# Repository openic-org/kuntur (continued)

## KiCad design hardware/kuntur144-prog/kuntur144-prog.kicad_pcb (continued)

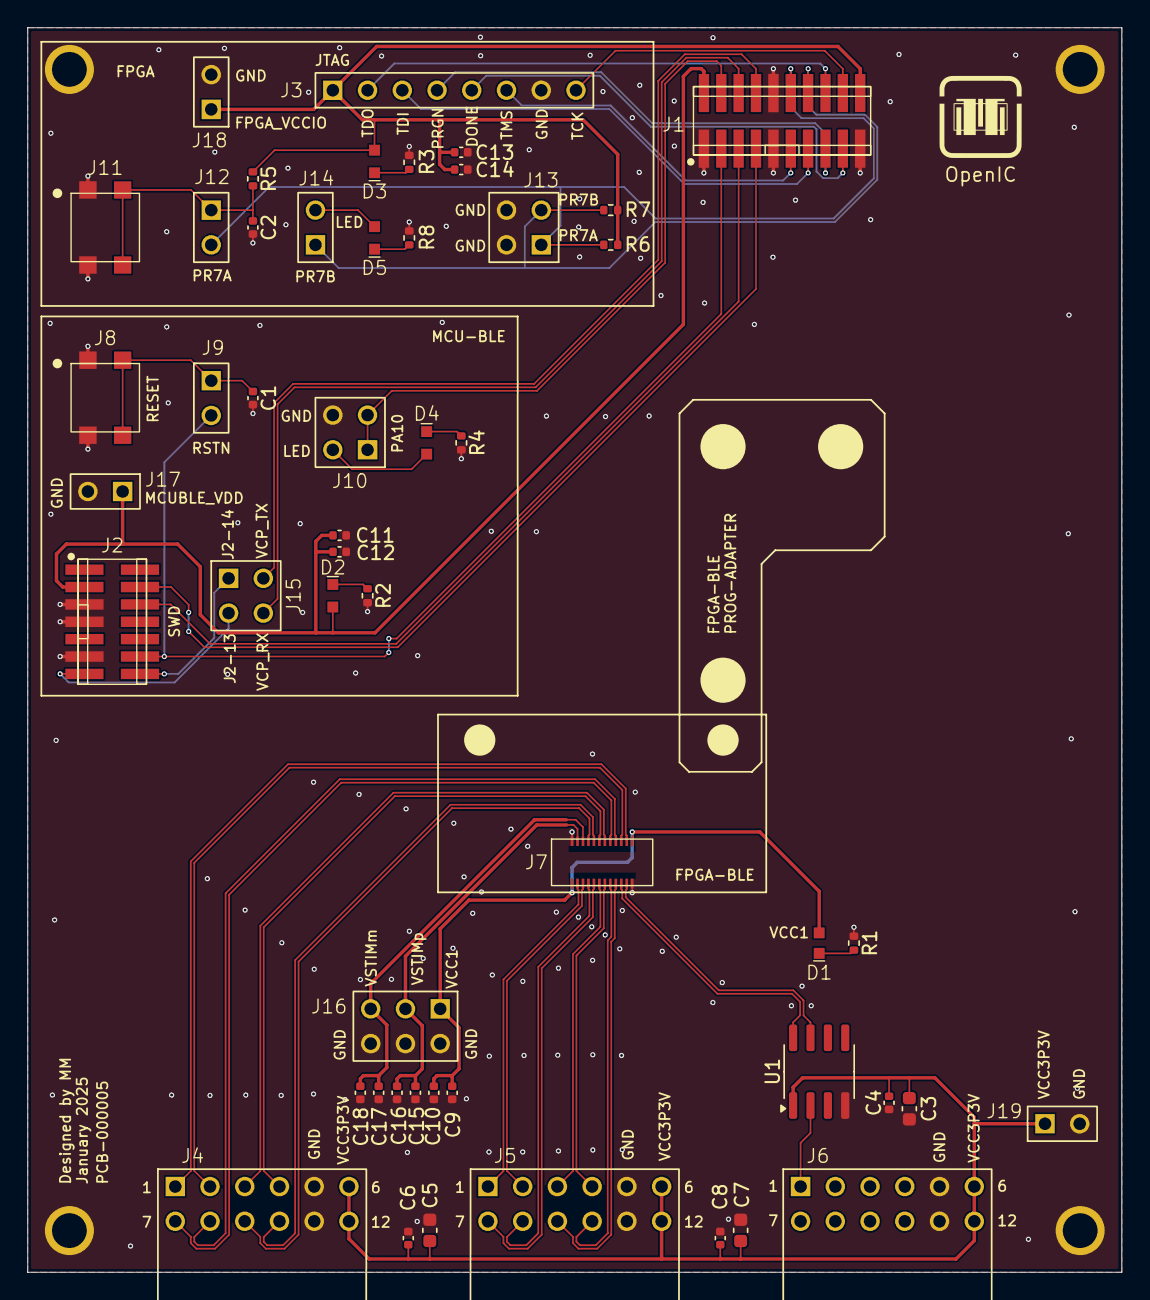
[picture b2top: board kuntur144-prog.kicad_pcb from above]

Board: 2 copper layers, 80.0 x 91.0 mm, 55 parts (0 on the bottom side), 51 nets.

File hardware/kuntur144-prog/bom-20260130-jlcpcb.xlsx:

Designator | Comment | Footprint
C1,C2,C4,C6,C8,C10,C12,C14,C16,C18 | 100n | GRM155R61C104KA88D
C3,C5,C7 | 10u | GRM185R60J106ME15J
C9,C11,C13,C15,C17 | 1u | GRM155R61C105KA12J
D1 | SMT Diode | LGQ396
D2,D3,D4,D5 | SMT Diode | CSL1901UW1
J1 | Connector | FTSH-110-01-L-DV-K
J2 | Connector | FTSH-107-01-L-DV-K
J3 | Headers | PH1-08-UA
J4,J5,J6 | Headers | PH2RA-12-UA
J7 | Connector | DF40C(2.0)-24DS-0.4V(51)
J8,J11 | Push-button | 7914G-1-000
J9,J12,J14,J17,J18,J19 | Headers | PH1-02-UA
J10,J13,J15 | Headers | M20-9760246
J16 | Headers | M20-9980346
R1,R2,R3,R4,R8 | 10 | RC0402FR-7W10RL
R5 | 10k | RC0402FR-7W10KL
R6,R7 | Do not populate | RC0402FR-7W4K7L
S1,S2,S3,S4 |  | None
U1 | LVDS to CMOS | ADN4661BRZ-REEL7

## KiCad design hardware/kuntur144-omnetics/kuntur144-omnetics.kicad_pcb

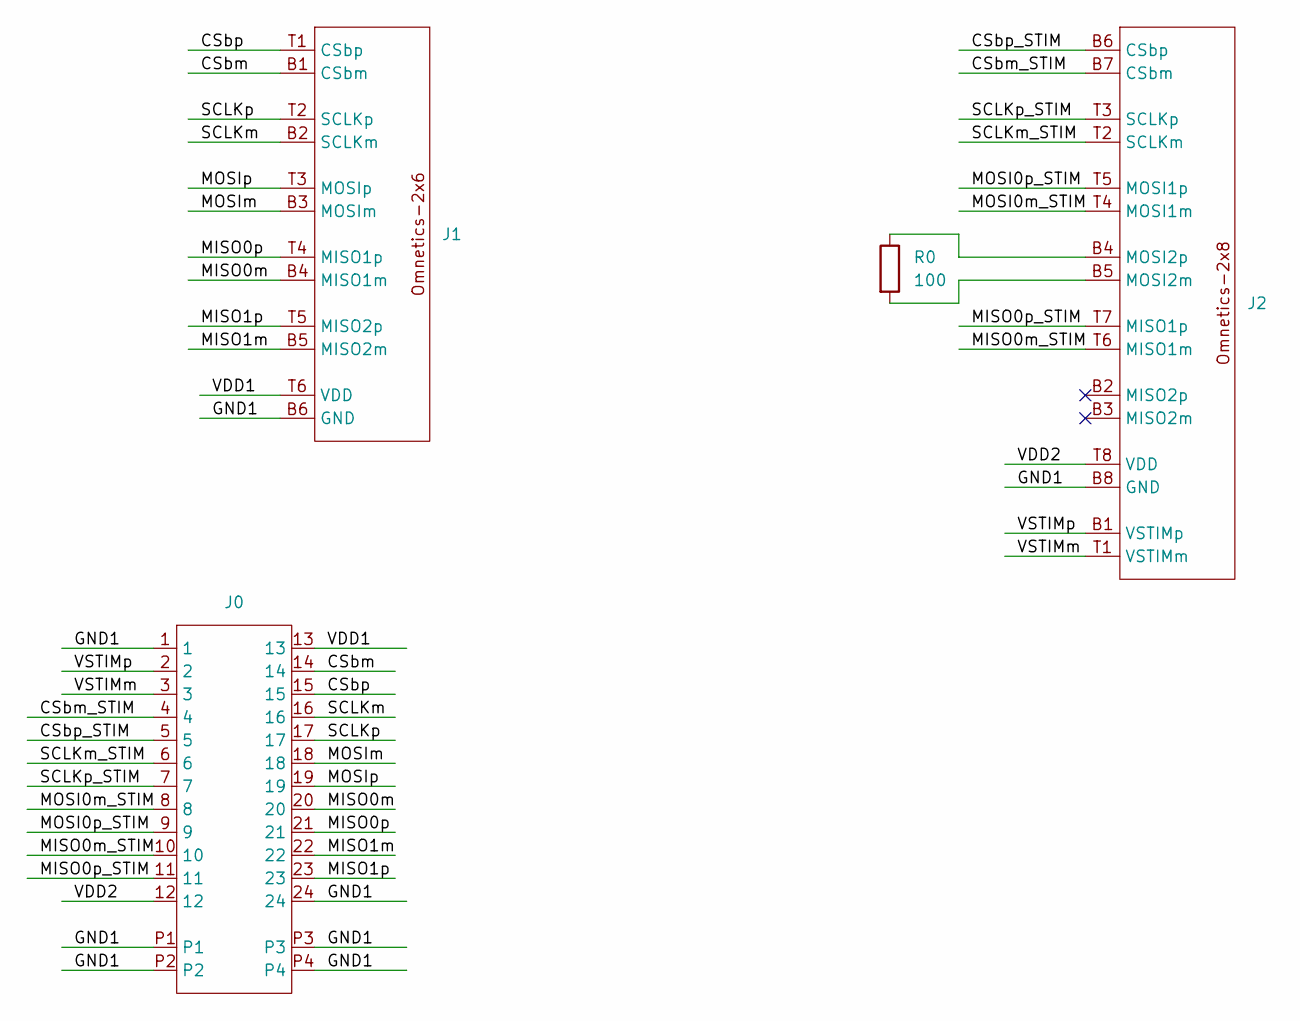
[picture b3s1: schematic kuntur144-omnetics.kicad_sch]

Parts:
J0: DF40C(2.0)-24DP-0.4V
J1: OMNETICS_PZN-12-AA; MPN A79623-001
J2: OMNETICS_PZN-16-AA; MPN A79633-001
R0: 100; R_0402_1005Metric

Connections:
/CSbm: J0.14, J1.B1 (CSbm)
/CSbm_STIM: J0.4, J2.B7 (CSbm)
/CSbp: J0.15, J1.T1 (CSbp)
/CSbp_STIM: J0.5, J2.B6 (CSbp)
/GND1: J0.1, J0.24, J0.P1, J0.P2, J0.P3, J0.P4, J1.B6 (GND), J2.B8 (GND)
/MISO0m: J0.20, J1.B4 (MISO1m)
/MISO0m_STIM: J0.10, J2.T6 (MISO1m)
/MISO0p: J0.21, J1.T4 (MISO1p)
/MISO0p_STIM: J0.11, J2.T7 (MISO1p)
/MISO1m: J0.22, J1.B5 (MISO2m)
/MISO1p: J0.23, J1.T5 (MISO2p)
/MOSI0m_STIM: J0.8, J2.T4 (MOSI1m)
/MOSI0p_STIM: J0.9, J2.T5 (MOSI1p)
/MOSIm: J0.18, J1.B3 (MOSIm)
/MOSIp: J0.19, J1.T3 (MOSIp)
/SCLKm: J0.16, J1.B2 (SCLKm)
/SCLKm_STIM: J0.6, J2.T2 (SCLKm)
/SCLKp: J0.17, J1.T2 (SCLKp)
/SCLKp_STIM: J0.7, J2.T3 (SCLKp)
/VDD1: J0.13, J1.T6 (VDD)
/VDD2: J0.12, J2.T8 (VDD)
/VSTIMm: J0.3, J2.T1 (VSTIMm)
/VSTIMp: J0.2, J2.B1 (VSTIMp)
unnamed: J2.B5 (MOSI2m), R0.2
unnamed: J2.B4 (MOSI2p), R0.1

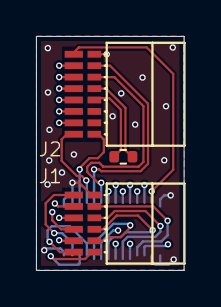
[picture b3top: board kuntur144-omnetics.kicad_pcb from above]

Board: 4 copper layers, 8.2 x 13.0 mm, 4 parts (1 on the bottom side), 25 nets.

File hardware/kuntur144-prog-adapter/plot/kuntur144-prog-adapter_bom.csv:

"Reference","Value","Qty","DNP","Manufacturer","MPN"
"J1","~","1","","Molex","5052742012"
"J2","~","1","","Samtec","FTSH-110-01-L-DV-K"

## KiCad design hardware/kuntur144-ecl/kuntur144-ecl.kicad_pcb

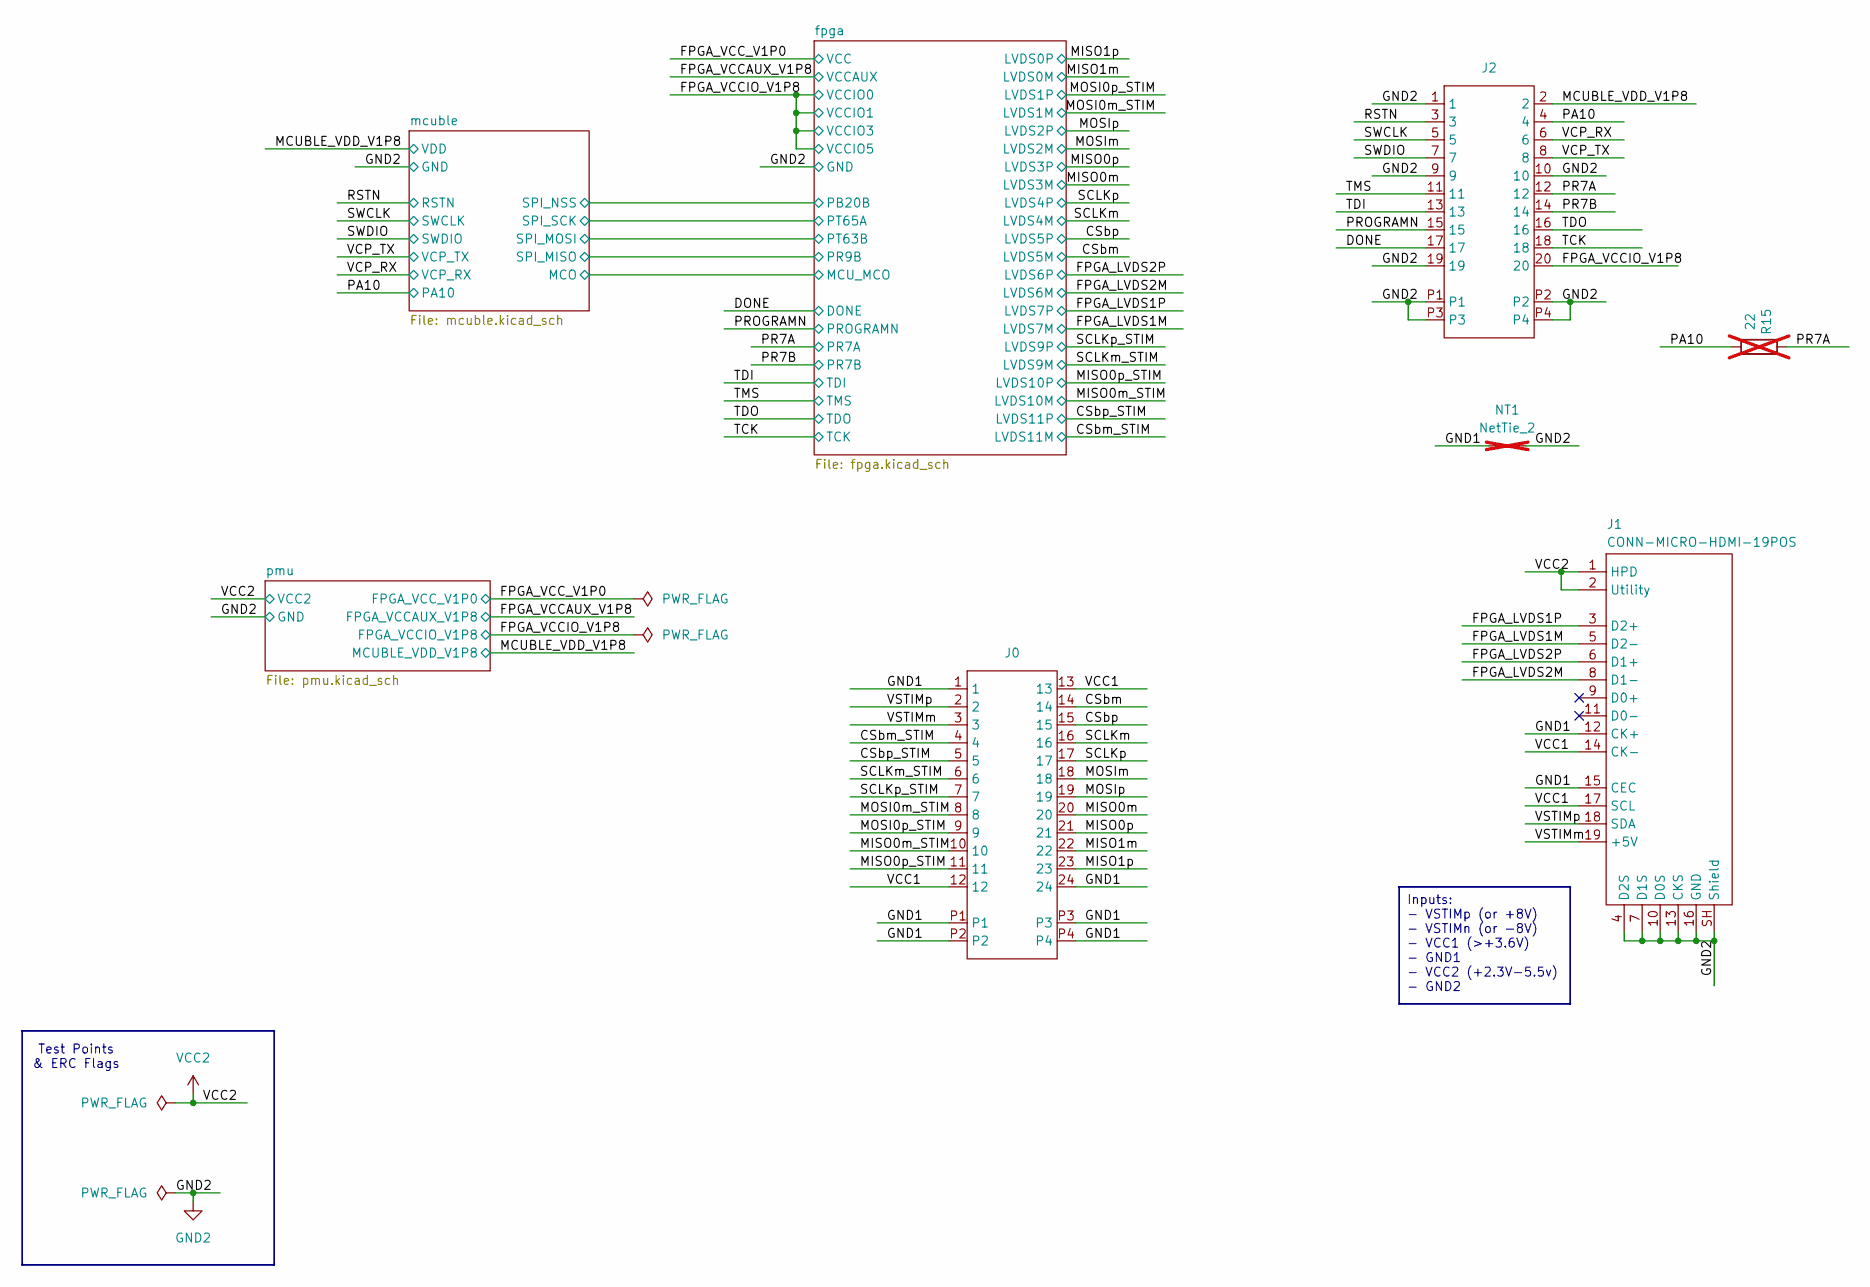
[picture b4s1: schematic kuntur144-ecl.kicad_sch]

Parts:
J0: DF40C(2.0)-24DP-0.4V; MPN DF40C-24DP-0.4V(51)
J1: CONN-MICRO-HDMI-19POS; HDMI_Micro-D_Molex_46765-0x01; MPN 0467650001
J2: CONN-MOLEX-MEZZ-20POS-P0.35mm; MPN 5052702012
NT1: NetTie_2; NetTie-2_SMD; not fitted
R15: 22; R_0402_1005Metric; MPN RC0402FR-0722RL; not fitted

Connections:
/CSbm: J0.14; also elsewhere on the board
/CSbm_STIM: J0.4; also elsewhere on the board
/CSbp: J0.15; also elsewhere on the board
/CSbp_STIM: J0.5; also elsewhere on the board
/DONE: J2.17; also elsewhere on the board
/FPGA_LVDS1M: J1.5 (D2-); also elsewhere on the board
/FPGA_LVDS1P: J1.3 (D2+); also elsewhere on the board
/FPGA_LVDS2M: J1.8 (D1-); also elsewhere on the board
/FPGA_LVDS2P: J1.6 (D1+); also elsewhere on the board
/FPGA_VCCIO_V1P8: J2.20; also elsewhere on the board
/GND1: J0.1, J0.24, J0.P1, J0.P2, J0.P3, J0.P4, J1.12 (CK+), J1.15 (CEC), NT1.1
/MCUBLE_VDD_V1P8: J2.2; also elsewhere on the board
/MISO0m: J0.20; also elsewhere on the board
/MISO0m_STIM: J0.10; also elsewhere on the board
/MISO0p: J0.21; also elsewhere on the board
/MISO0p_STIM: J0.11; also elsewhere on the board
/MISO1m: J0.22; also elsewhere on the board
/MISO1p: J0.23; also elsewhere on the board
/MOSI0m_STIM: J0.8; also elsewhere on the board
/MOSI0p_STIM: J0.9; also elsewhere on the board
/MOSIm: J0.18; also elsewhere on the board
/MOSIp: J0.19; also elsewhere on the board
/PA10: J2.4, R15.1; also elsewhere on the board
/PR7A: J2.12, R15.2; also elsewhere on the board
/PR7B: J2.14; also elsewhere on the board
/PROGRAMN: J2.15; also elsewhere on the board
/RSTN: J2.3; also elsewhere on the board
/SCLKm: J0.16; also elsewhere on the board
/SCLKm_STIM: J0.6; also elsewhere on the board
/SCLKp: J0.17; also elsewhere on the board
/SCLKp_STIM: J0.7; also elsewhere on the board
/SWCLK: J2.5; also elsewhere on the board
/SWDIO: J2.7; also elsewhere on the board
/TCK: J2.18; also elsewhere on the board
/TDI: J2.13; also elsewhere on the board
/TDO: J2.16; also elsewhere on the board
/TMS: J2.11; also elsewhere on the board
/VCC1: J0.12, J0.13, J1.14 (CK-), J1.17 (SCL)
/VCP_RX: J2.6; also elsewhere on the board
/VCP_TX: J2.8; also elsewhere on the board
/VSTIMm: J0.3, J1.19 (+5V)
/VSTIMp: J0.2, J1.18 (SDA)
GND2: J1.4 (D2S), J1.7 (D1S), J1.10 (D0S), J1.13 (CKS), J1.16 (GND), J1.SH (Shield), J2.1, J2.9, J2.10, J2.19, J2.P1, J2.P2, J2.P3, J2.P4, NT1.2; also elsewhere on the board
VCC2: J1.1 (HPD), J1.2 (Utility); also elsewhere on the board

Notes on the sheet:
Inputs: - VSTIMp (or +8V) - VSTIMn (or -8V) - VCC1 (>+3.6V) - GND1 - VCC2 (+2.3V-5.5v) - GND2
Test Points & ERC Flags

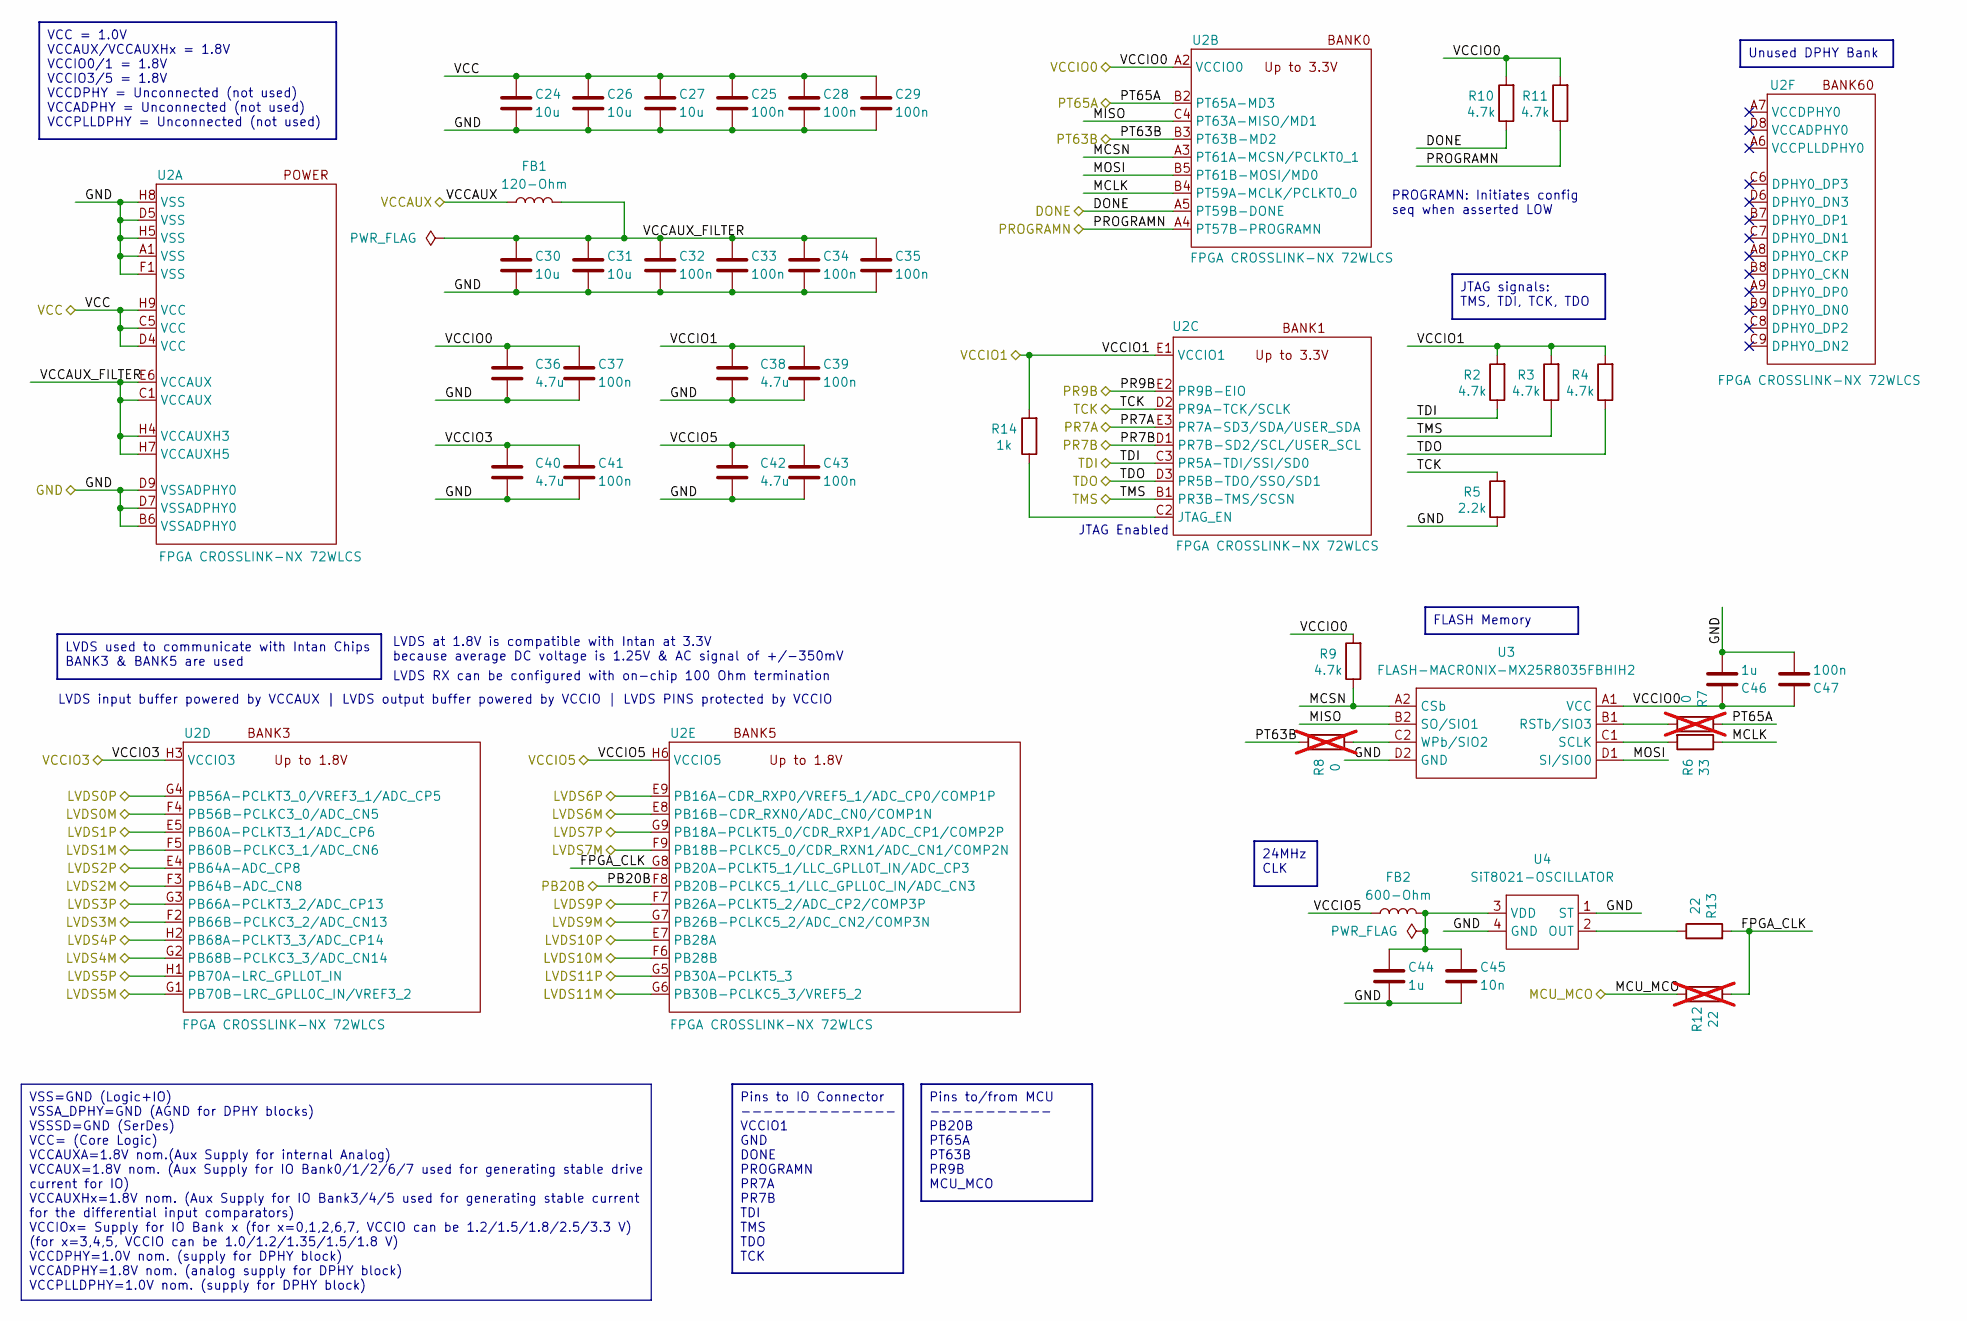
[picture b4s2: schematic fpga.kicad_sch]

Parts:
C24, C26, C27, C30, C31: 10u; SMD_C_0603_10UF_6.3V_GRM185R60J106ME15; MPN GRM185R60J106ME15J
C25, C28, C29, C32, C33, C34, C35, C37, C39, C41, C43, C47: 100n; C_0201_0603Metric; MPN C0603X5R1C104K030BC
C36, C38, C40, C42: 4.7u; C_0402_1005Metric; MPN KGM05CR51C475MH
C44, C46: 1u; C_0201_0603Metric; MPN GRM033R61C105ME15D
C45: 10n; C_0201_0603Metric; MPN GRM033R61C103KA12D
FB1: 120-Ohm; L_0402_1005Metric; MPN MPZ1005S121CT000
FB2: 600-Ohm; L_0402_1005Metric; MPN BLM15AX601SN1D
R2, R3, R4, R9, R10, R11: 4.7k; R_0201_0603Metric; MPN RC0201FR-074K7L
R5: 2.2k; R_0201_0603Metric; MPN RC0201FR-072K2L
R6: 33; R_0201_0603Metric; MPN RC0201FR-0733RL
R7, R8: 0; R_0201_0603Metric; MPN RC0201FR-070RL; not fitted
R12: 22; R_0402_1005Metric; MPN RC0402FR-0722RL; not fitted
R13: 22; R_0402_1005Metric; MPN RC0402FR-0722RL
R14: 1k; R_0201_0603Metric; MPN RC0201FR-071KL
U2: BGA-72_9x8_4.1x3.8mm; MPN LIFCL-17-7UWG72C
U3: FLASH-MACRONIX-MX25R8035FBHIH2; MX25R8035FBHIH2-WLCSP-8; MPN MX25R8035FBHIH2
U4: SiT8021-OSCILLATOR; SiTime-4LD-1.5x0.8x0.55mm; MPN SIT8021AC-J4-18S-24.000000

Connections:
/CSbm: U2.G1 (PB70B-LRC_GPLL0C_IN/VREF3_2); also elsewhere on the board
/CSbm_STIM: U2.G6 (PB30B-PCLKC5_3/VREF5_2); also elsewhere on the board
/CSbp: U2.H1 (PB70A-LRC_GPLL0T_IN); also elsewhere on the board
/CSbp_STIM: U2.G5 (PB30A-PCLKT5_3); also elsewhere on the board
/DONE: R10.1, U2.A5 (PT59B-DONE); also elsewhere on the board
/FPGA_LVDS1M: U2.F9 (PB18B-PCLKC5_0/CDR_RXN1/ADC_CN1/COMP2N); also elsewhere on the board
/FPGA_LVDS1P: U2.G9 (PB18A-PCLKT5_0/CDR_RXP1/ADC_CP1/COMP2P); also elsewhere on the board
/FPGA_LVDS2M: U2.E8 (PB16B-CDR_RXN0/ADC_CN0/COMP1N); also elsewhere on the board
/FPGA_LVDS2P: U2.E9 (PB16A-CDR_RXP0/VREF5_1/ADC_CP0/COMP1P); also elsewhere on the board
/FPGA_VCCAUX_V1P8: FB1.2; also elsewhere on the board
/FPGA_VCCIO_V1P8: C36.1, C37.1, C38.1, C39.1, C40.1, C41.1, C42.1, C43.1, C46.1, C47.1, FB2.2, R2.2, R3.2, R4.2, R9.2, R10.2, R11.2, R14.2, U2.A2 (VCCIO0), U2.E1 (VCCIO1), U2.H3 (VCCIO3), U2.H6 (VCCIO5), U3.A1 (VCC); also elsewhere on the board
/FPGA_VCC_V1P0: C24.1, C25.1, C26.1, C27.1, C28.1, C29.1, U2.C5 (VCC), U2.D4 (VCC), U2.H9 (VCC); also elsewhere on the board
/MISO0m: U2.F2 (PB66B-PCLKC3_2/ADC_CN13); also elsewhere on the board
/MISO0m_STIM: U2.F6 (PB28B); also elsewhere on the board
/MISO0p: U2.G3 (PB66A-PCLKT3_2/ADC_CP13); also elsewhere on the board
/MISO0p_STIM: U2.E7 (PB28A); also elsewhere on the board
/MISO1m: U2.F4 (PB56B-PCLKC3_0/ADC_CN5); also elsewhere on the board
/MISO1p: U2.G4 (PB56A-PCLKT3_0/VREF3_1/ADC_CP5); also elsewhere on the board
/MOSI0m_STIM: U2.F5 (PB60B-PCLKC3_1/ADC_CN6); also elsewhere on the board
/MOSI0p_STIM: U2.E5 (PB60A-PCLKT3_1/ADC_CP6); also elsewhere on the board
/MOSIm: U2.F3 (PB64B-ADC_CN8); also elsewhere on the board
/MOSIp: U2.E4 (PB64A-ADC_CP8); also elsewhere on the board
/PR7A: U2.E3 (PR7A-SD3/SDA/USER_SDA); also elsewhere on the board
/PR7B: U2.D1 (PR7B-SD2/SCL/USER_SCL); also elsewhere on the board
/PROGRAMN: R11.1, U2.A4 (PT57B-PROGRAMN); also elsewhere on the board
/SCLKm: U2.G2 (PB68B-PCLKC3_3/ADC_CN14); also elsewhere on the board
/SCLKm_STIM: U2.G7 (PB26B-PCLKC5_2/ADC_CN2/COMP3N); also elsewhere on the board
/SCLKp: U2.H2 (PB68A-PCLKT3_3/ADC_CP14); also elsewhere on the board
/SCLKp_STIM: U2.F7 (PB26A-PCLKT5_2/ADC_CP2/COMP3P); also elsewhere on the board
/TCK: R5.2, U2.D2 (PR9A-TCK/SCLK); also elsewhere on the board
/TDI: R2.1, U2.C3 (PR5A-TDI/SSI/SD0); also elsewhere on the board
/TDO: R4.1, U2.D3 (PR5B-TDO/SSO/SD1); also elsewhere on the board
/TMS: R3.1, U2.B1 (PR3B-TMS/SCSN); also elsewhere on the board
/fpga/FPGA_CLK: R12.1, R13.2, U2.G8 (PB20A-PCLKT5_1/LLC_GPLL0T_IN/ADC_CP3)
/fpga/MCLK: R6.1, U2.B4 (PT59A-MCLK/PCLKT0_0)
/fpga/MCSN: R9.1, U2.A3 (PT61A-MCSN/PCLKT0_1), U3.A2 (CSb)
/fpga/MCU_MCO: R12.2; also elsewhere on the board
/fpga/MISO: U2.C4 (PT63A-MISO/MD1), U3.B2 (SO/SIO1)
/fpga/MOSI: U2.B5 (PT61B-MOSI/MD0), U3.D1 (SI/SIO0)
/fpga/PB20B: U2.F8 (PB20B-PCLKC5_1/LLC_GPLL0C_IN/ADC_CN3); also elsewhere on the board
/fpga/PR9B: U2.E2 (PR9B-EIO); also elsewhere on the board
/fpga/PT63B: R8.2, U2.B3 (PT63B-MD2); also elsewhere on the board
/fpga/PT65A: R7.2, U2.B2 (PT65A-MD3); also elsewhere on the board
/fpga/VCCAUX_FILTER: C30.1, C31.1, C32.1, C33.1, C34.1, C35.1, FB1.1, U2.C1 (VCCAUX), U2.E6 (VCCAUX), U2.H4 (VCCAUXH3), U2.H7 (VCCAUXH5)
GND2: C24.2, C25.2, C26.2, C27.2, C28.2, C29.2, C30.2, C31.2, C32.2, C33.2, C34.2, C35.2, C36.2, C37.2, C38.2, C39.2, C40.2, C41.2, C42.2, C43.2, C44.2, C45.2, C46.2, C47.2, R5.1, U2.A1 (VSS), U2.B6 (VSSADPHY0), U2.D5 (VSS), U2.D7 (VSSADPHY0), U2.D9 (VSSADPHY0), U2.F1 (VSS), U2.H5 (VSS), U2.H8 (VSS), U3.D2 (GND), U4.1 (ST), U4.4 (GND); also elsewhere on the board
unnamed: R14.1, U2.C2 (JTAG_EN)
unnamed: R7.1, U3.B1 (RSTb/SIO3)
unnamed: R6.2, U3.C1 (SCLK)
unnamed: R8.1, U3.C2 (WPb/SIO2)
unnamed: R13.1, U4.2 (OUT)
unnamed: C44.1, C45.1, FB2.1, U4.3 (VDD)

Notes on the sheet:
VSS=GND (Logic+IO) VSSA_DPHY=GND (AGND for DPHY blocks) VSSSD=GND (SerDes) VCC= (Core Logic) VCCAUXA=1.8V nom.(Aux Supply for internal Analog) VCCAUX=1.8V nom. (Aux Supply for IO Bank0/1/2/6/7 used for generating stable drive current for IO) VCCAUXHx=1.8V nom. (Aux Supply for IO Bank3/4/5 used for 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
FLASH Memory
24MHz CLK
VCC = 1.0V VCCAUX/VCCAUXHx = 1.8V VCCIO0/1 = 1.8V VCCIO3/5 = 1.8V VCCDPHY = Unconnected (not used) VCCADPHY = Unconnected (not used) VCCPLLDPHY = Unconnected (not used)
Pins to IO Connector -------------- VCCIO1 GND DONE PROGRAMN PR7A PR7B TDI TMS TDO TCK
JTAG signals: TMS, TDI, TCK, TDO
Pins to/from MCU ----------- PB20B PT65A PT63B PR9B MCU_MCO
LVDS used to communicate with Intan Chips BANK3 & BANK5 are used
Unused DPHY Bank
JTAG Enabled
PROGRAMN: Initiates config seq when asserted LOW
LVDS RX can be configured with on-chip 100 Ohm termination
LVDS input buffer powered by VCCAUX | LVDS output buffer powered by VCCIO | LVDS PINS protected by VCCIO
LVDS at 1.8V is compatible with Intan at 3.3V because average DC voltage is 1.25V & AC signal of +/-350mV

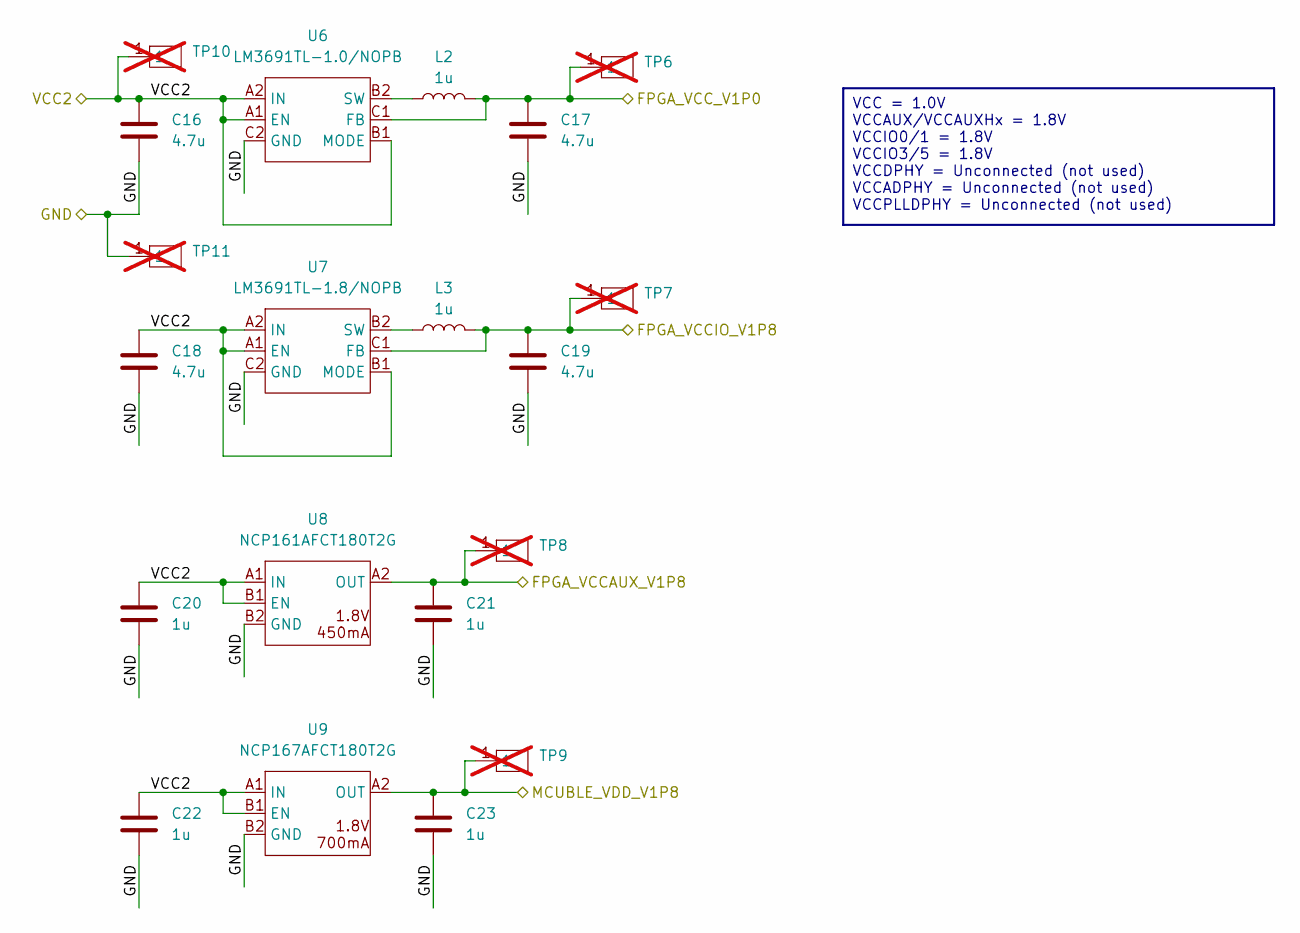
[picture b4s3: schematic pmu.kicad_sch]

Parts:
C16, C17, C18, C19: 4.7u; C_0402_1005Metric; MPN KGM05CR51C475MH
C20, C21, C22, C23: 1u; C_0201_0603Metric; MPN GRM033R61C105ME15D
L2, L3: 1u; SMD_L_0805_1UH_MLZ2012; MPN MLZ2012A1R0WT000
TP6, TP7, TP8, TP9, TP10, TP11: TESTPOINT_PAD_SQ_0.5; not fitted
U6: LM3691TL-1.0/NOPB; DSBGA-6-P0.5; MPN LM3691TL-1.0/NOPB
U7: LM3691TL-1.8/NOPB; DSBGA-6-P0.5; MPN LM3691TL-1.8/NOPB
U8: NCP161AFCT180T2G; WLCSP-4-P0.35; MPN NCP161AFCT180T2G
U9: NCP167AFCT180T2G; WLCSP-4-P0.35; MPN NCP167AFCT180T2G

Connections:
/FPGA_VCCAUX_V1P8: C21.1, TP8.1, U8.A2 (OUT); also elsewhere on the board
/FPGA_VCCIO_V1P8: C19.1, L3.2, TP7.1, U7.C1 (FB); also elsewhere on the board
/FPGA_VCC_V1P0: C17.1, L2.2, TP6.1, U6.C1 (FB); also elsewhere on the board
/MCUBLE_VDD_V1P8: C23.1, TP9.1, U9.A2 (OUT); also elsewhere on the board
GND2: C16.2, C17.2, C18.2, C19.2, C20.2, C21.2, C22.2, C23.2, TP11.1, U6.C2 (GND), U7.C2 (GND), U8.B2 (GND), U9.B2 (GND); also elsewhere on the board
unnamed: L2.1, U6.B2 (SW)
unnamed: L3.1, U7.B2 (SW)
VCC2: C16.1, C18.1, C20.1, C22.1, TP10.1, U6.A1 (EN), U6.A2 (IN), U6.B1 (MODE), U7.A1 (EN), U7.A2 (IN), U7.B1 (MODE), U8.A1 (IN), U8.B1 (EN), U9.A1 (IN), U9.B1 (EN); also elsewhere on the board

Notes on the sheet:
VCC = 1.0V VCCAUX/VCCAUXHx = 1.8V VCCIO0/1 = 1.8V VCCIO3/5 = 1.8V VCCDPHY = Unconnected (not used) VCCADPHY = Unconnected (not used) VCCPLLDPHY = Unconnected (not used)

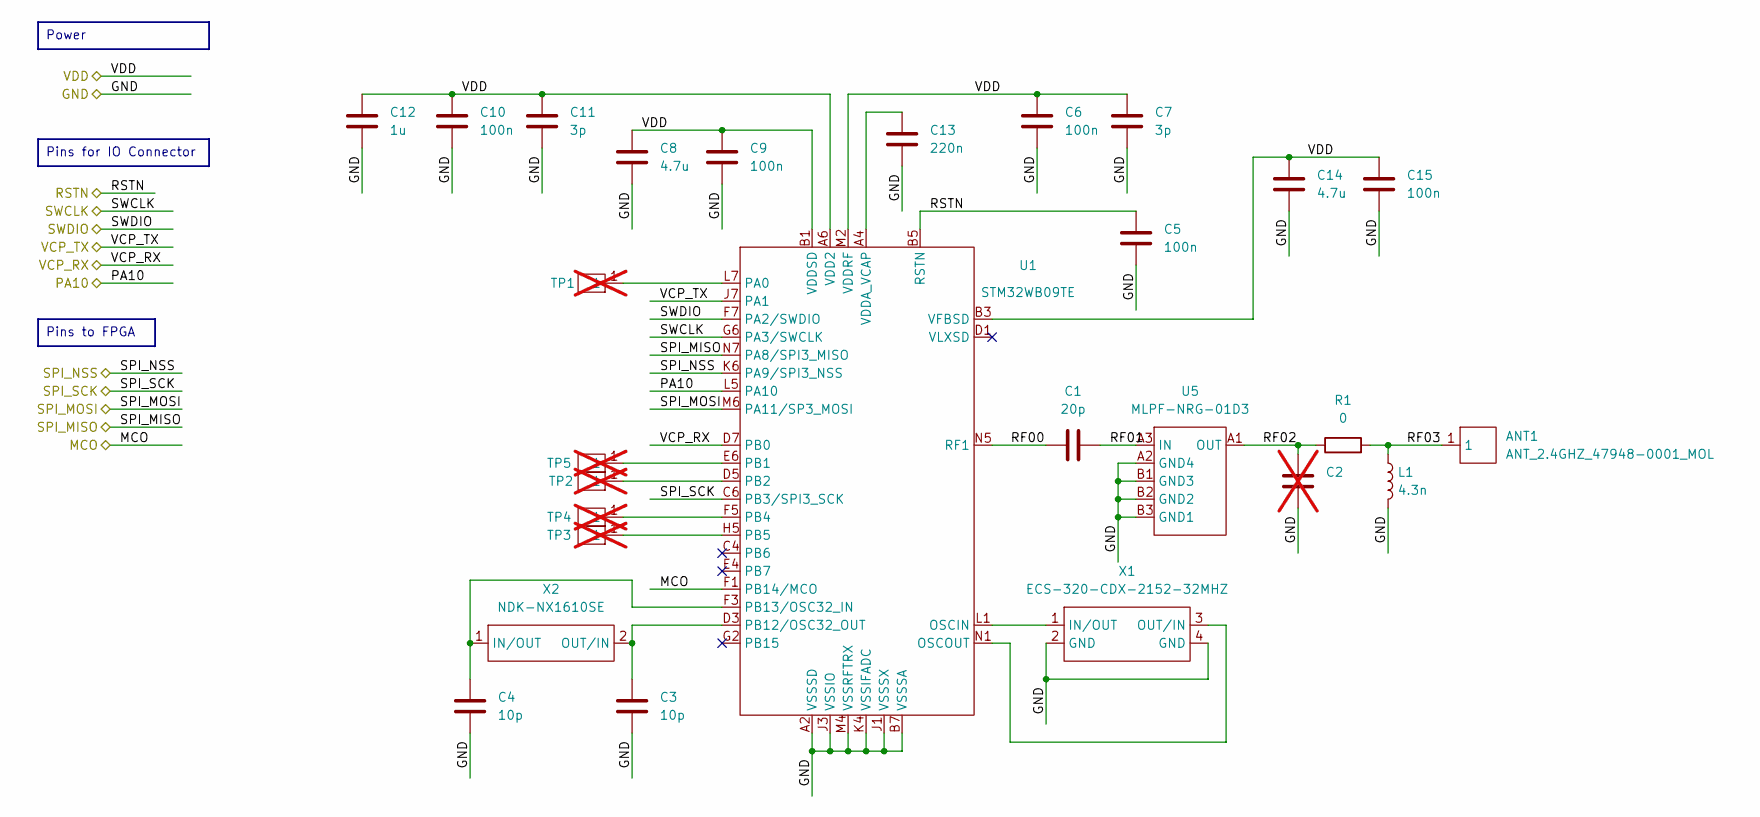
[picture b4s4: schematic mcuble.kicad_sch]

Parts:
ANT1: ANT_2.4GHZ_47948-0001_MOL; ANT_47948-0001_MOL; MPN 0479480001
C1: 20p; SMD-0201; MPN GJM0335C1E200GB01
C2: SMD-0201; MPN GJM0335C1E2R0WB01D; not fitted
C3, C4: 10p; C_0201_0603Metric; MPN GJM0335C1E100GB01D
C5, C6, C9, C10, C15: 100n; C_0201_0603Metric; MPN C0603X5R1C104K030BC
C7, C11: 3p; C_0201_0603Metric; MPN GJM0335C1E3R0BB01D
C8, C14: 4.7u; C_0402_1005Metric; MPN KGM05CR51C475MH
C12: 1u; C_0201_0603Metric; MPN GRM033R61C105ME15D
C13: 220n; C_0201_0603Metric; MPN C0603X5R1C224K030BC
L1: 4.3n; SMD-0402; MPN LQG15HS4N3B02D
R1: 0; SMD-0201; MPN RC0201FR-070RL
TP1, TP2, TP3, TP4, TP5: TESTPOINT_PAD_SQ_0.5; not fitted
U1: BGA-36_STM32WB09TE_2.8x3mm; MPN STM32WB09TEF7TR
U5: MLPF-NRG-01D3; ST-CSPG-6; MPN MLPF-NRG-01D3
X1: ECS-320-CDX-2152-32MHZ; CRYSTAL-ECS-320-CDX-2152-32MHZ; MPN ECS-320-CDX-2152
X2: NDK-NX1610SE; CRYSTAL-NDK-MU01500-32.768K; MPN MU01500-32.768K

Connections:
/MCUBLE_VDD_V1P8: C6.1, C7.1, C8.1, C9.1, C10.1, C11.1, C12.1, C14.1, C15.1, U1.A6 (VDD2), U1.B1 (VDDSD), U1.B3 (VFBSD), U1.M2 (VDDRF); also elsewhere on the board
/PA10: U1.L5 (PA10); also elsewhere on the board
/RSTN: C5.1, U1.B5 (RSTN); also elsewhere on the board
/SWCLK: U1.G6 (PA3/SWCLK); also elsewhere on the board
/SWDIO: U1.F7 (PA2/SWDIO); also elsewhere on the board
/VCP_RX: U1.D7 (PB0); also elsewhere on the board
/VCP_TX: U1.J7 (PA1); also elsewhere on the board
/fpga/MCU_MCO: U1.F1 (PB14/MCO); also elsewhere on the board
/fpga/PB20B: U1.K6 (PA9/SPI3_NSS); also elsewhere on the board
/fpga/PR9B: U1.N7 (PA8/SPI3_MISO); also elsewhere on the board
/fpga/PT63B: U1.M6 (PA11/SP3_MOSI); also elsewhere on the board
/fpga/PT65A: U1.C6 (PB3/SPI3_SCK); also elsewhere on the board
/mcuble/RF00: C1.1, U1.N5 (RF1)
/mcuble/RF01: C1.2, U5.A3 (IN)
/mcuble/RF02: C2.2, R1.1, U5.A1 (OUT)
/mcuble/RF03: ANT1.1, L1.1, R1.2
GND2: C2.1, C3.2, C4.2, C5.2, C6.2, C7.2, C8.2, C9.2, C10.2, C11.2, C12.2, C13.2, C14.2, C15.2, L1.2, U1.A2 (VSSSD), U1.B7 (VSSSA), U1.J1 (VSSSX), U1.J3 (VSSIO), U1.K4 (VSSIFADC), U1.M4 (VSSRFTRX), U5.A2 (GND4), U5.B1 (GND3), U5.B2 (GND2), U5.B3 (GND1), X1.2 (GND), X1.4 (GND); also elsewhere on the board
unnamed: U1.L1 (OSCIN), X1.1 (IN/OUT)
unnamed: U1.N1 (OSCOUT), X1.3 (OUT/IN)
unnamed: TP1.1, U1.L7 (PA0)
unnamed: TP5.1, U1.E6 (PB1)
unnamed: TP2.1, U1.D5 (PB2)
unnamed: TP4.1, U1.F5 (PB4)
unnamed: TP3.1, U1.H5 (PB5)
unnamed: C3.1, U1.D3 (PB12/OSC32_OUT), X2.2 (OUT/IN)
unnamed: C4.1, U1.F3 (PB13/OSC32_IN), X2.1 (IN/OUT)
unnamed: C13.1, U1.A4 (VDDA_VCAP)

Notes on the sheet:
Pins for IO Connector
Power
Pins to FPGA

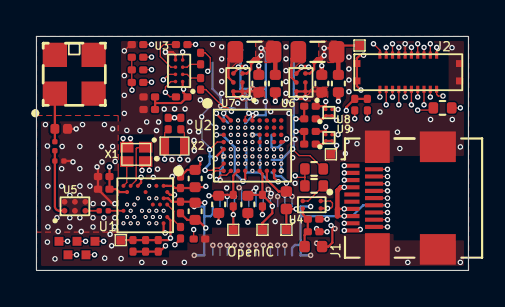
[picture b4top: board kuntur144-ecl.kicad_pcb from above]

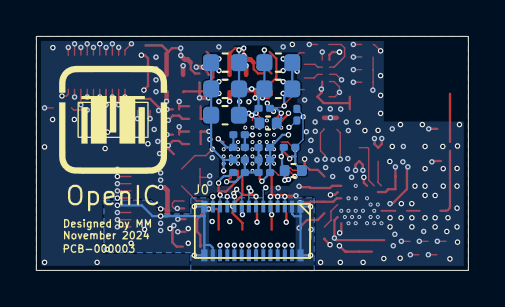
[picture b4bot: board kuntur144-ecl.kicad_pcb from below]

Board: 8 copper layers, 24.0 x 13.0 mm, 94 parts (18 on the bottom side), 79 nets.

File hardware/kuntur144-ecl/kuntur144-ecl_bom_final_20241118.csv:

"Reference","Value","Datasheet","Footprint","Qty","DNP","MPN","Manufacturer"
"ANT1","ANT_2.4GHZ_47948-0001_MOL","","openic:ANT_47948-0001_MOL","1","","0479480001","Molex"
"C1","20p","~","openic:SMD-0201","1","","GJM0335C1E200GB01","Murata Electronics"
"C2","~","~","openic:SMD-0201","1","DNP","GJM0335C1E2R0WB01D","Murata Electronics"
"C3,C4","10p","~","Capacitor_SMD:C_0201_0603Metric","2","","GJM0335C1E100GB01D","Murata Electronics"
"C5,C6,C9,C10,C15,C25,C28,C29,C32,C33,C34,C35,C37,C39,C41,C43,C47","100n","~","Capacitor_SMD:C_0201_0603Metric","17","","C0603X5R1C104K030BC","TDK"
"C7,C11","3p","~","Capacitor_SMD:C_0201_0603Metric","2","","GJM0335C1E3R0BB01D","Murata Electronics"
"C8,C14,C16,C17,C18,C19,C36,C38,C40,C42","4.7u","~","Capacitor_SMD:C_0402_1005Metric","10","","KGM05CR51C475MH","Kyocera AVX"
"C12,C20,C21,C22,C23,C44,C46","1u","~","Capacitor_SMD:C_0201_0603Metric","7","","GRM033R61C105ME15D","Murata Electronics"
"C13","220n","~","Capacitor_SMD:C_0201_0603Metric","1","","C0603X5R1C224K030BC","TDK"
"C24,C26,C27,C30,C31","10u","~","openic:SMD_C_0603_10UF_6.3V_GRM185R60J106ME15","5","","GRM185R60J106ME15J","Murata Electronics"
"C45","10n","~","Capacitor_SMD:C_0201_0603Metric","1","","GRM033R61C103KA12D ","Murata Electronics"
"FB1","120-Ohm","~","Inductor_SMD:L_0402_1005Metric","1","","MPZ1005S121CT000","TDK"
"FB2","600-Ohm","~","Inductor_SMD:L_0402_1005Metric","1","","BLM15AX601SN1D","Murata Electronics"
"J0","~","","openic:DF40C(2.0)-24DP-0.4V","1","","DF40C-24DP-0.4V(51)","Hirose Electric"
"J1","CONN-MICRO-HDMI-19POS","","openic:HDMI_Micro-D_Molex_46765-0x01","1","","0467650001","Molex"
"J2","~","","openic:CONN-MOLEX-MEZZ-20POS-P0.35mm","1","","5052702012","Molex"
"L1","4.3n","~","openic:SMD-0402","1","","LQG15HS4N3B02D","Murata Electronics"
"L2,L3","1u","~","openic:SMD_L_0805_1UH_MLZ2012","2","","MLZ2012A1R0WT000","TDK"
"R1","0","~","openic:SMD-0201","1","","RC0201FR-070RL","Yageo"
"R2,R3,R4,R9,R10,R11","4.7k","~","Resistor_SMD:R_0201_0603Metric","6","","RC0201FR-074K7L","Yageo"
"R5","2.2k","~","Resistor_SMD:R_0201_0603Metric","1","","RC0201FR-072K2L","Yageo"
"R6","33","~","Resistor_SMD:R_0201_0603Metric","1","","RC0201FR-0733RL","Yageo"
"R7,R8","0","~","Resistor_SMD:R_0201_0603Metric","2","DNP","RC0201FR-070RL","Yageo"
"R12,R15","22","~","Resistor_SMD:R_0402_1005Metric","2","DNP","RC0402FR-0722RL","Yageo"
"R13","22","~","Resistor_SMD:R_0402_1005Metric","1","","RC0402FR-0722RL","Yageo"
"R14","1k","~","Resistor_SMD:R_0201_0603Metric","1","","RC0201FR-071KL","Yageo"
"TP1,TP2,TP3,TP4,TP5,TP6,TP7,TP8,TP9,TP10,TP11","~","","openic:TESTPOINT_PAD_SQ_0.5","11","DNP","",""
"U1","~","","openic:BGA-36_STM32WB09TE_2.8x3mm","1","","STM32WB09TEF7TR","ST Microelectronics"
"U2","~","","openic:BGA-72_9x8_4.1x3.8mm","1","","LIFCL-17-7UWG72C","Lattice Semiconductor"
"U3","FLASH-MACRONIX-MX25R8035FBHIH2","","openic:MX25R8035FBHIH2-WLCSP-8","1","","MX25R8035FBHIH2","Macronix"
"U4","SiT8021-OSCILLATOR","","openic:SiTime-4LD-1.5x0.8x0.55mm","1","","SIT8021AC-J4-18S-24.000000","SiTime"
"U5","MLPF-NRG-01D3","","openic:ST-CSPG-6","1","","MLPF-NRG-01D3","ST Microelectronics"
"U6","LM3691TL-1.0/NOPB","","openic:DSBGA-6-P0.5","1","","LM3691TL-1.0/NOPB","TI"
"U7","LM3691TL-1.8/NOPB","","openic:DSBGA-6-P0.5","1","","LM3691TL-1.8/NOPB","TI"
"U8","NCP161AFCT180T2G","","openic:WLCSP-4-P0.35","1","","NCP161AFCT180T2G","OnSemi"
"U9","NCP167AFCT180T2G","","openic:WLCSP-4-P0.35","1","","NCP167AFCT180T2G","OnSemi"
"X1","ECS-320-CDX-2152-32MHZ","","openic:CRYSTAL-ECS-320-CDX-2152-32MHZ","1","","ECS-320-CDX-2152","ECS"
"X2","NDK-NX1610SE","","openic:CRYSTAL-NDK-MU01500-32.768K","1","","MU01500-32.768K","NDK"
